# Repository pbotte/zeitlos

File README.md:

# Ladensystem für einen automatischen Dorfladen

Ein Paket aus Soft- und Hardware für ein automatisches Ladensystem, welches sich für kleine Läden, bis ca. 1000 Produkte, eignet. Das System basiert darauf, dass jedes Produkt durch eine eigene Waage gewogen wird, welche mit einem Computer verbunden ist.

## Beschreibung eines typischen Einkaufs:
1. Einlass mit Girocard oder Kreditkarte. Dabei findet eine Vorauthorisierung (Reservierung von Geld) statt.
2. Der Kunde betritt den Laden und entnimmt die Waren selbst aus den Regalen. Die Anzeige der entnommen Waren und Massen erfolgt sofort und automatisch auf den Kundendisplays.
3. Zum Abschluss des Einkaufs verlässt der Kunde den Laden. Die Abrechnung erfolgt anschließend automatisch über die Karte ohne dass die Karte erneut vorgezeigt werden muss.

Es kann immer nur ein Kunde gleichzeitig einkaufen.

## Hinweise
* [Kostenübersicht](kostenuebersicht.md)

## Technische Details 
* [Zustände eines Einkaufs](ablauf.md)
* [Bestandteile des Ladens / MQTT-Übersicht](MQTT_Overview.md)
* In den jeweiligen Unterordnern gibt es weitere Markdown-Dateien mit Erläuterungen zur Installation und Befehlen.
* Zum gleichzeitigen Herunterladen der Submodule: 
  ```bash
  git clone --recurse-submodules  git@github.com:pbotte/zeitlos.git
  ```

## Lizenz
Alle Soft- und Hardware stehen unter der [GPL v3](https://github.com/pbotte/zeitlos/blob/master/LICENSE) zur freien Verfügung.

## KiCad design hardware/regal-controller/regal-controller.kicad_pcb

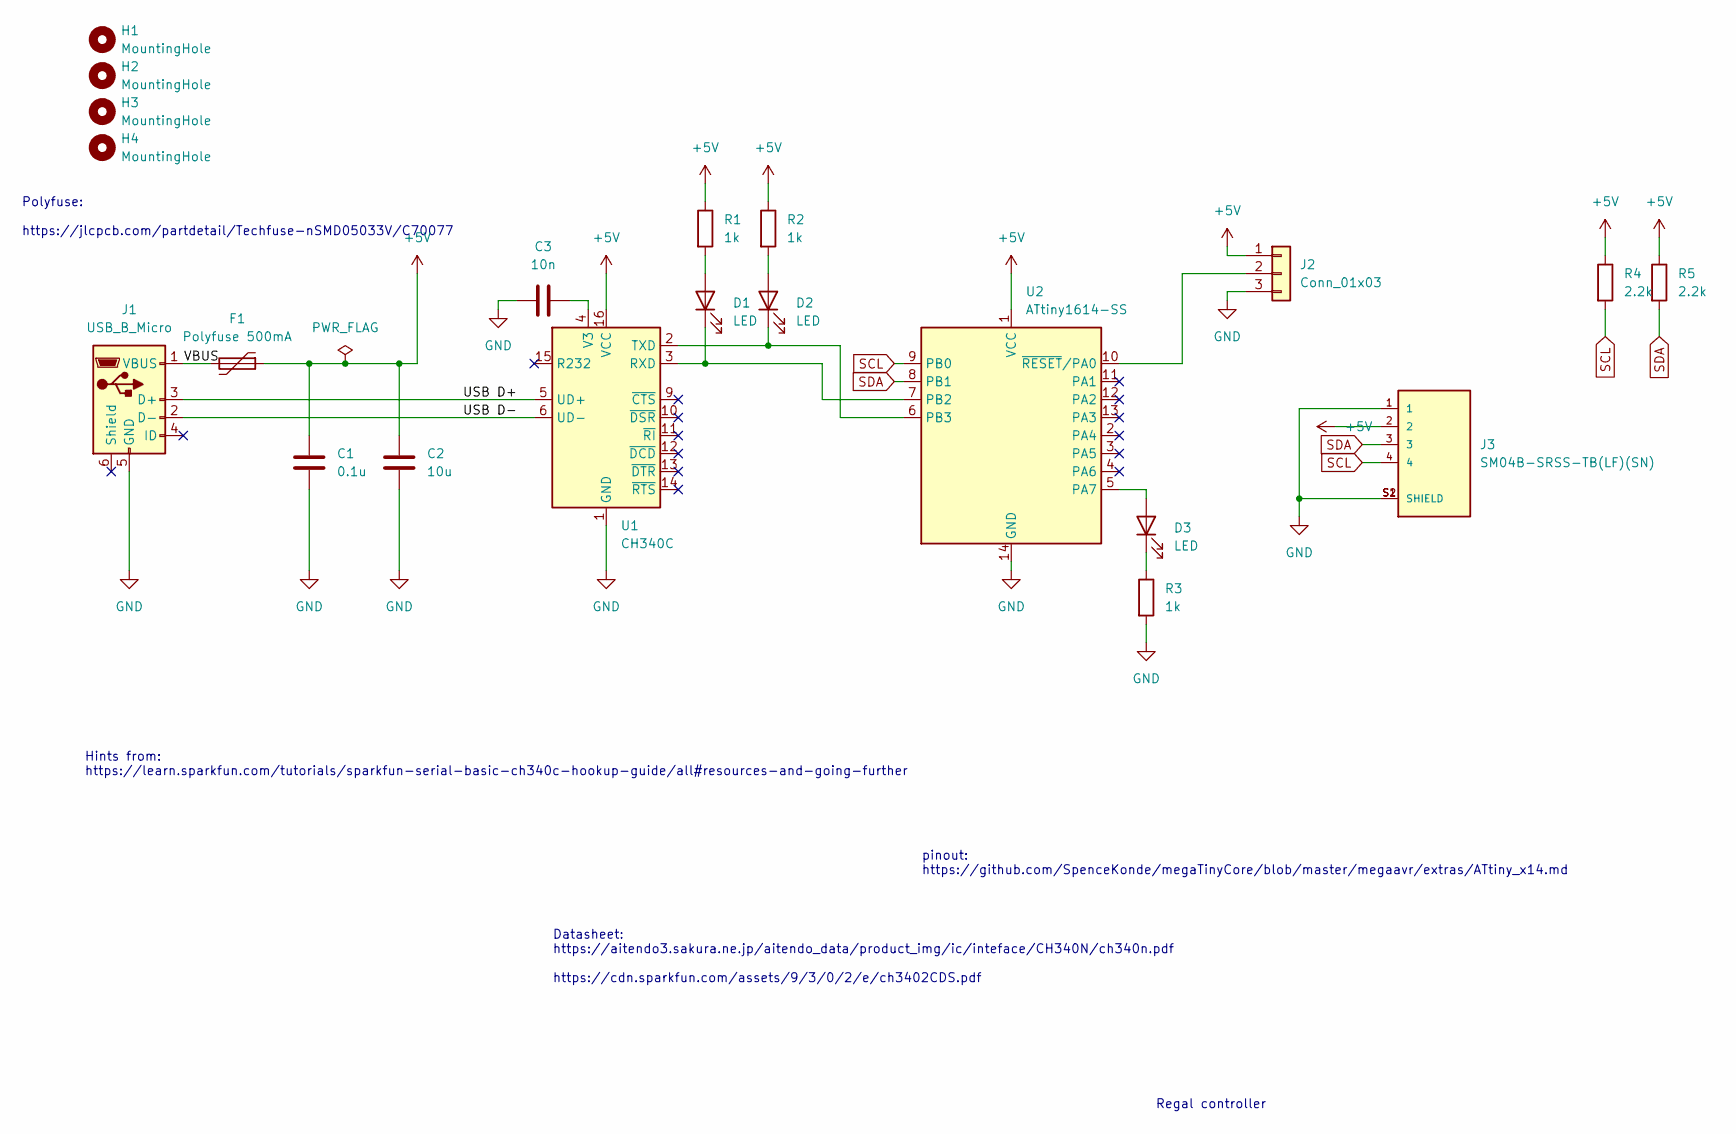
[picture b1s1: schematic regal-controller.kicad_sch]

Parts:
C1: 0.1u; C_1206_3216Metric
C2: 10u; C_1206_3216Metric
C3: 10n; C_1206_3216Metric
D1, D2, D3: LED; LED_1206_3216Metric
F1: Polyfuse 500mA; Fuse_1206_3216Metric
H1, H2, H3, H4: MountingHole; MountingHole_3.2mm_M3
J1: USB_B_Micro; USB_Micro-B_XKB_U254-051T-4BH83-F1S
J2: Conn_01x03; PinSocket_1x03_P2.54mm_Vertical
J3: SM04B-SRSS-TB(LF)(SN); JST_SM04B-SRSS-TB(LF)(SN)
R1, R2, R3: 1k; R_1206_3216Metric
R4, R5: 2.2k; R_1206_3216Metric
U1: CH340C; SOIC-16_3.9x9.9mm_P1.27mm
U2: ATtiny1614-SS; SOIC-14_3.9x8.7mm_P1.27mm

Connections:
+5V: C1.1, C2.1, F1.1, J2.1, J3.2, R1.1, R2.1, R4.1, R5.1, U1.16 (VCC), U2.1 (VCC)
/USB D+: J1.3 (D+), U1.5 (UD+)
/USB D-: J1.2 (D-), U1.6 (UD-)
/VBUS: F1.2, J1.1 (VBUS)
GND: C1.2, C2.2, C3.1, J1.5 (GND), J2.3, J3.1, J3.S1 (SHIELD), J3.S2 (SHIELD), R3.2, U1.1 (GND), U2.14 (GND)
unnamed: D1.2 (A), R1.2
unnamed: D1.1 (K), U1.3 (RXD), U2.7 (PB2)
unnamed: D2.2 (A), R2.2
unnamed: D2.1 (K), U1.2 (TXD), U2.6 (PB3)
unnamed: D3.2 (A), U2.5 (PA7)
unnamed: D3.1 (K), R3.1
unnamed: J2.2, U2.10 (~RESET/PA0)
unnamed: C3.2, U1.4 (V3)
SCL: J3.4, R4.2, U2.9 (PB0)
SDA: J3.3, R5.2, U2.8 (PB1)

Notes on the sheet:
Regal controller
pinout: https://github.com/SpenceKonde/megaTinyCore/blob/master/megaavr/extras/ATtiny_x14.md
Polyfuse: https://jlcpcb.com/partdetail/Techfuse-nSMD05033V/C70077
Datasheet: https://aitendo3.sakura.ne.jp/aitendo_data/product_img/ic/inteface/CH340N/ch340n.pdf https://cdn.sparkfun.com/assets/9/3/0/2/e/ch3402CDS.pdf
Hints from: https://learn.sparkfun.com/tutorials/sparkfun-serial-basic-ch340c-hookup-guide/all#resources-and-going-further

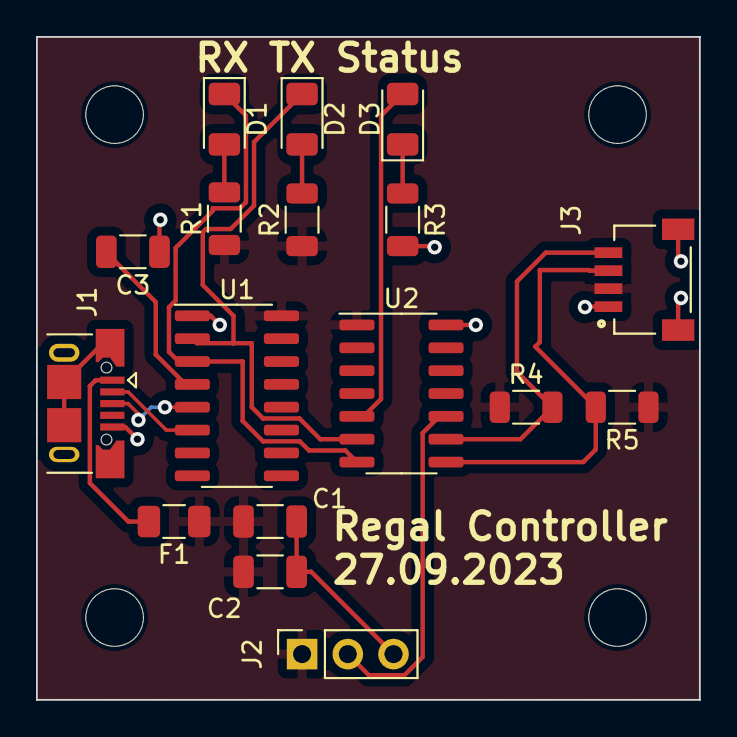
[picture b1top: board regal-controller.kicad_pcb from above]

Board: 2 copper layers, 36.8 x 36.8 mm, 21 parts (0 on the bottom side), 15 nets.

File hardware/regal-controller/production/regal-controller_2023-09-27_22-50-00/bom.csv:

Designator,Footprint,Quantity,Value,LCSC Part #
C1,1206,1,0.1u,
C2,1206,1,10u,
C3,1206,1,10n,
"D1, D2, D3",1206,3,LED,
F1,1206,1,Polyfuse 500mA,
"H1, H2, H3, H4",MountingHole_3.2mm_M3,4,MountingHole,
J1,USB_Micro-B_XKB_U254-051T-4BH83-F1S,1,USB_B_Micro,
J2,PinSocket_1x03_P2.54mm_Vertical,1,Conn_01x03,
J3,JST_SM04B-SRSS-TB(LF)(SN),1,SM04B-SRSS-TB(LF)(SN),
"R1, R2, R3",1206,3,1k,
"R4, R5",1206,2,2.2k,
U1,SOIC-16_3.9x9.9mm_P1.27mm,1,CH340C,
U2,SOIC-14_3.9x8.7mm_P1.27mm,1,ATtiny1614-SS,

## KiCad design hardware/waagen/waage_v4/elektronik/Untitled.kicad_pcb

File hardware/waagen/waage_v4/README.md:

# Waage V4

* Waage aus 3D Drucker
* Wiegen mit Wägezellen

Kosten: Etwa 25€/Waage mit Druck und Elektornik.
Stand: Prototyp, aktuell in der Entwicklung. 

3D-Daten: https://cad.onshape.com/documents/e93dca015aaa1e9e19b301b1/w/7b48b7bfd47193fa3707ac4f/e/e2c3e895b10e82bbda4e5613?renderMode=0&uiState=649b429d2a16ba7928158867

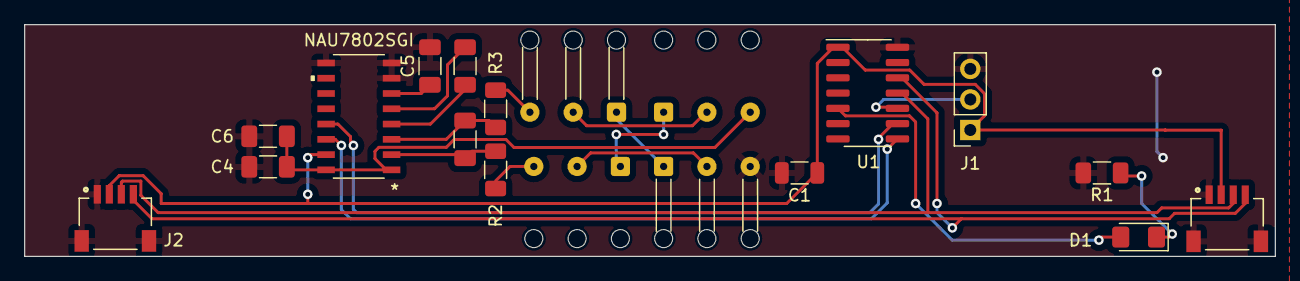
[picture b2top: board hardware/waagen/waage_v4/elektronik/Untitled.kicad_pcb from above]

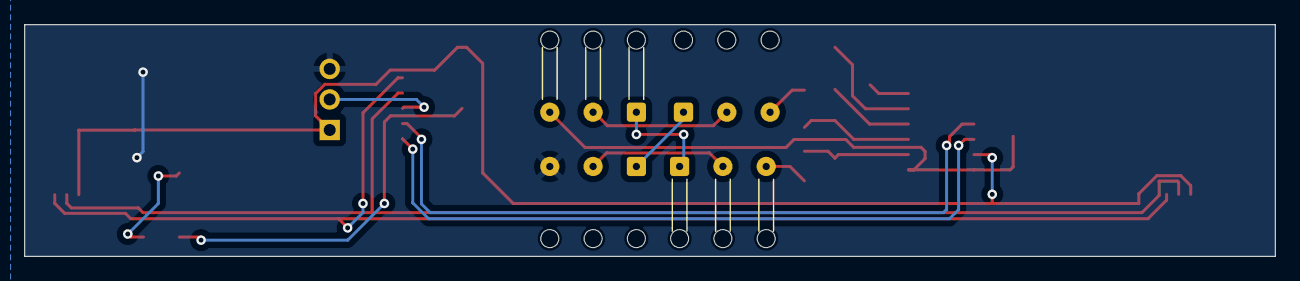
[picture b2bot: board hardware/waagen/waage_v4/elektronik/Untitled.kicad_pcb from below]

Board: 2 copper layers, 104.0 x 19.3 mm, 19 parts (2 on the bottom side), 21 nets.

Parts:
C1: 10u; C_1206_3216Metric
C2, C5, C6: 100n; C_1206_3216Metric_Pad1.33x1.80mm_HandSolder
C3: 330p; C_1206_3216Metric_Pad1.33x1.80mm_HandSolder
C4: 1µ; C_1206_3216Metric_Pad1.33x1.80mm_HandSolder
D1: LED; LED_1206_3216Metric_Pad1.42x1.75mm_HandSolder
J1: Conn_01x03; PinSocket_1x03_P2.54mm_Vertical
J2, J3: SM04B-SRSS-TB(LF)(SN); JST_SM04B-SRSS-TB(LF)(SN)
J4, J5, J6, J7: Conn_01x03_Male; SolderWire-0.1sqmm_1x03_P3.6mm_D0.4mm_OD1mm_Relief
R1: 180; R_1206_3216Metric_Pad1.30x1.75mm_HandSolder
R2, R3: 47; R_1206_3216Metric_Pad1.30x1.75mm_HandSolder
U1: ATtiny1614-SS; SOIC-14_3.9x8.7mm_P1.27mm
U2: NAU7802SGI

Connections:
/SCL_0: U1.9 (PB0), U2.13 (SCLK)
/SDA_0: U1.8 (PB1), U2.14 (SDIO)
/Scale/NAU_VDDA: C4.1, C6.1, J7.3, U2.1 (REFP), U2.16 (AVDD/LDO)
GND: C1.2, C4.2, C5.2, C6.2, J1.3, J2.1, J2.S1 (SHIELD), J2.S2 (SHIELD), J3.1, J3.S1 (SHIELD), J3.S2 (SHIELD), J4.3, R1.2, U1.14 (GND), U2.7 (REFN), U2.8 (AVSS), U2.9 (DVSS)
unnamed: D1.2 (A), U1.5 (PA7)
unnamed: D1.1 (K), R1.1
unnamed: J1.2, U1.10 (~RESET/PA0)
unnamed: J4.1, J6.1
unnamed: J4.2, J5.2
unnamed: J5.1, J7.1
unnamed: J5.3, R2.1
unnamed: J6.2, J7.2
unnamed: J6.3, R3.1
unnamed: C5.1, U2.6 (VBG)
unnamed: C2.1, R2.2, U2.2 (VIN1N)
unnamed: C2.2, R3.2, U2.3 (VIN1P)
unnamed: C3.1, U2.4 (VIN2N)
unnamed: C3.2, U2.5 (VIN2P)
SCL_1: J2.4, J3.4, U1.12 (PA2)
SDA_1: J2.3, J3.3, U1.11 (PA1)
VCC: C1.1, J1.1, J2.2, J3.2, U1.1 (VCC), U2.15 (DVDD)

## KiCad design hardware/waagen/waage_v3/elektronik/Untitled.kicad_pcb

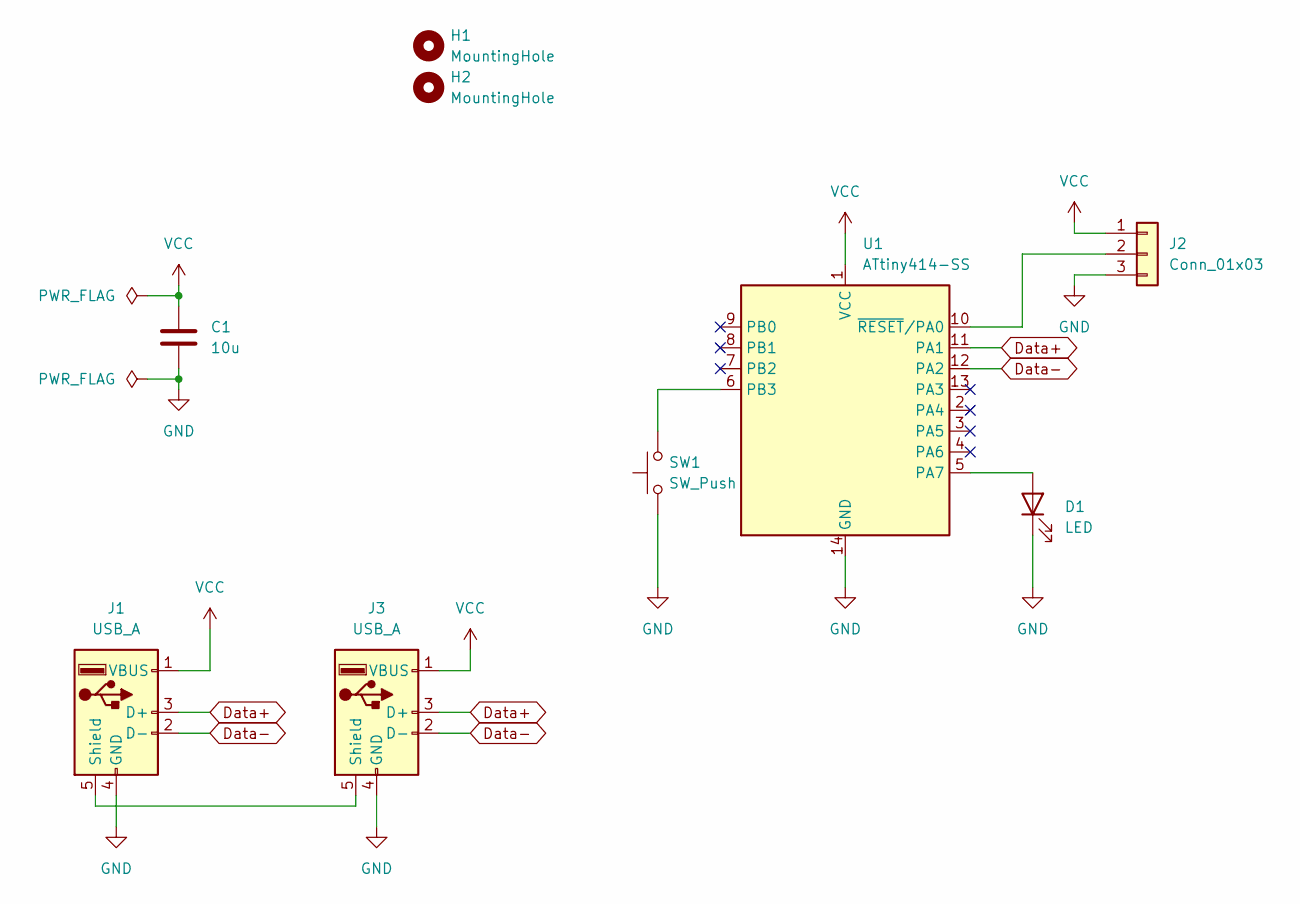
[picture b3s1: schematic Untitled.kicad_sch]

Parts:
C1: 10u; C_1206_3216Metric
D1: LED; LED_D5.0mm_Horizontal_O3.81mm_Z9.0mm
H1, H2: MountingHole; MountingHole_2.5mm
J1: USB_A; Conn_USB_A_Jack
J2: Conn_01x03; PinSocket_1x03_P2.54mm_Vertical
J3: USB_A; Conn_USB_A_Plug
SW1: SW_Push; Button_Switch_ESE-11MV1T
U1: ATtiny414-SS; SOIC-14_3.9x8.7mm_P1.27mm

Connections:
Data+: J1.3 (D+), J3.3 (D+), U1.11 (PA1)
Data-: J1.2 (D-), J3.2 (D-), U1.12 (PA2)
GND: C1.2, D1.1 (K), J1.4 (GND), J2.3, J3.4 (GND), SW1.1, U1.14 (GND)
unnamed: D1.2 (A), U1.5 (PA7)
unnamed: J1.5 (Shield), J3.5 (Shield)
unnamed: J2.2, U1.10 (~RESET/PA0)
unnamed: SW1.2, U1.6 (PB3)
VCC: C1.1, J1.1 (VBUS), J2.1, J3.1 (VBUS), U1.1 (VCC)

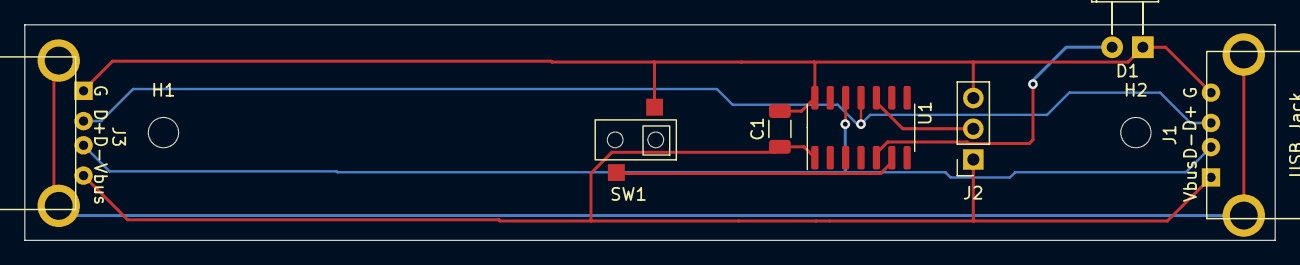
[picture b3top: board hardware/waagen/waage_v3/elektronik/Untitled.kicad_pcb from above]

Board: 2 copper layers, 103.2 x 17.8 mm, 9 parts (0 on the bottom side), 8 nets.

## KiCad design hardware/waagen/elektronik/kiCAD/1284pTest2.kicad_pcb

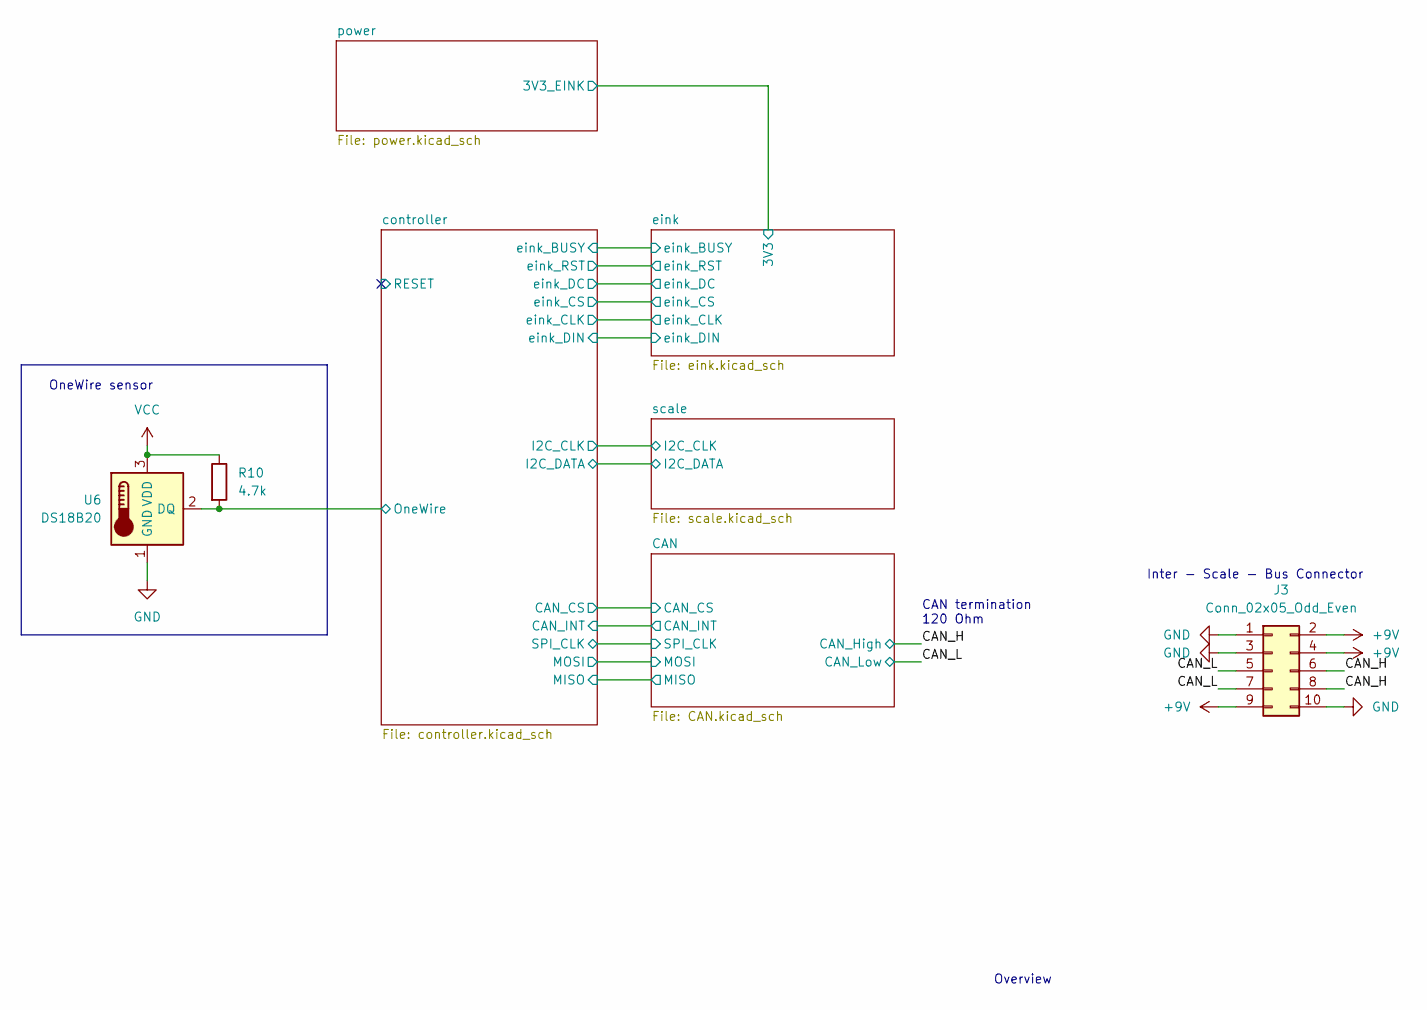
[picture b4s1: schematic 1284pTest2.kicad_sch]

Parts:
J3: Conn_02x05_Odd_Even; PinSocket_2x05_P2.54mm_Horizontal
R10: 4.7k; R_1206_3216Metric_Pad1.30x1.75mm_HandSolder
U6: DS18B20; TO-92

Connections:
+9V: J3.2, J3.4, J3.9; also elsewhere on the board
/CAN_H: J3.6, J3.8; also elsewhere on the board
/CAN_L: J3.5, J3.7; also elsewhere on the board
/controller/OneWire: R10.2, U6.2 (DQ); also elsewhere on the board
GND: J3.1, J3.3, J3.10, U6.1 (GND); also elsewhere on the board
VCC: R10.1, U6.3 (VDD); also elsewhere on the board

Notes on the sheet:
CAN termination 120 Ohm
Inter - Scale - Bus Connector
Overview
OneWire sensor

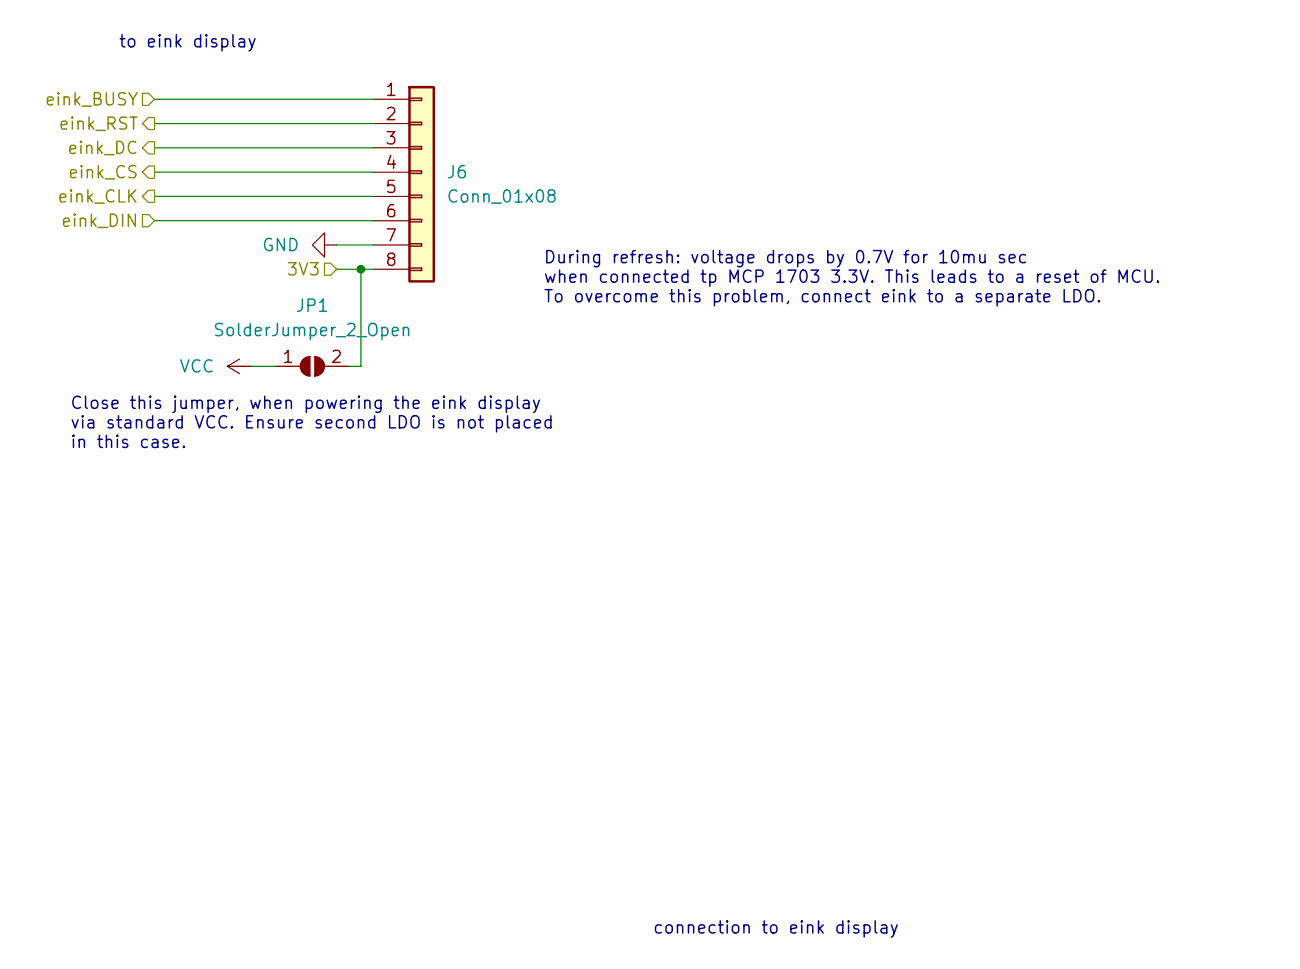
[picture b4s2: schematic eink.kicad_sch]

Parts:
J6: Conn_01x08; PinHeader_1x08_P2.54mm_Horizontal
JP1: SolderJumper_2_Open; SolderJumper-2_P1.3mm_Open_RoundedPad1.0x1.5mm

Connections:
/controller/eink_BUSY: J6.1; also elsewhere on the board
/controller/eink_CLK: J6.5; also elsewhere on the board
/controller/eink_CS: J6.4; also elsewhere on the board
/controller/eink_DC: J6.3; also elsewhere on the board
/controller/eink_DIN: J6.6; also elsewhere on the board
/controller/eink_RST: J6.2; also elsewhere on the board
/power/3V3_EINK: J6.8, JP1.2 (B); also elsewhere on the board
GND: J6.7; also elsewhere on the board
VCC: JP1.1 (A); also elsewhere on the board

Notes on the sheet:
to eink display
Close this jumper, when powering the eink display via standard VCC. Ensure second LDO is not placed in this case.
During refresh: voltage drops by 0.7V for 10mu sec when connected tp MCP 1703 3.3V. This leads to a reset of MCU. To overcome this problem, connect eink to a separate LDO.
connection to eink display

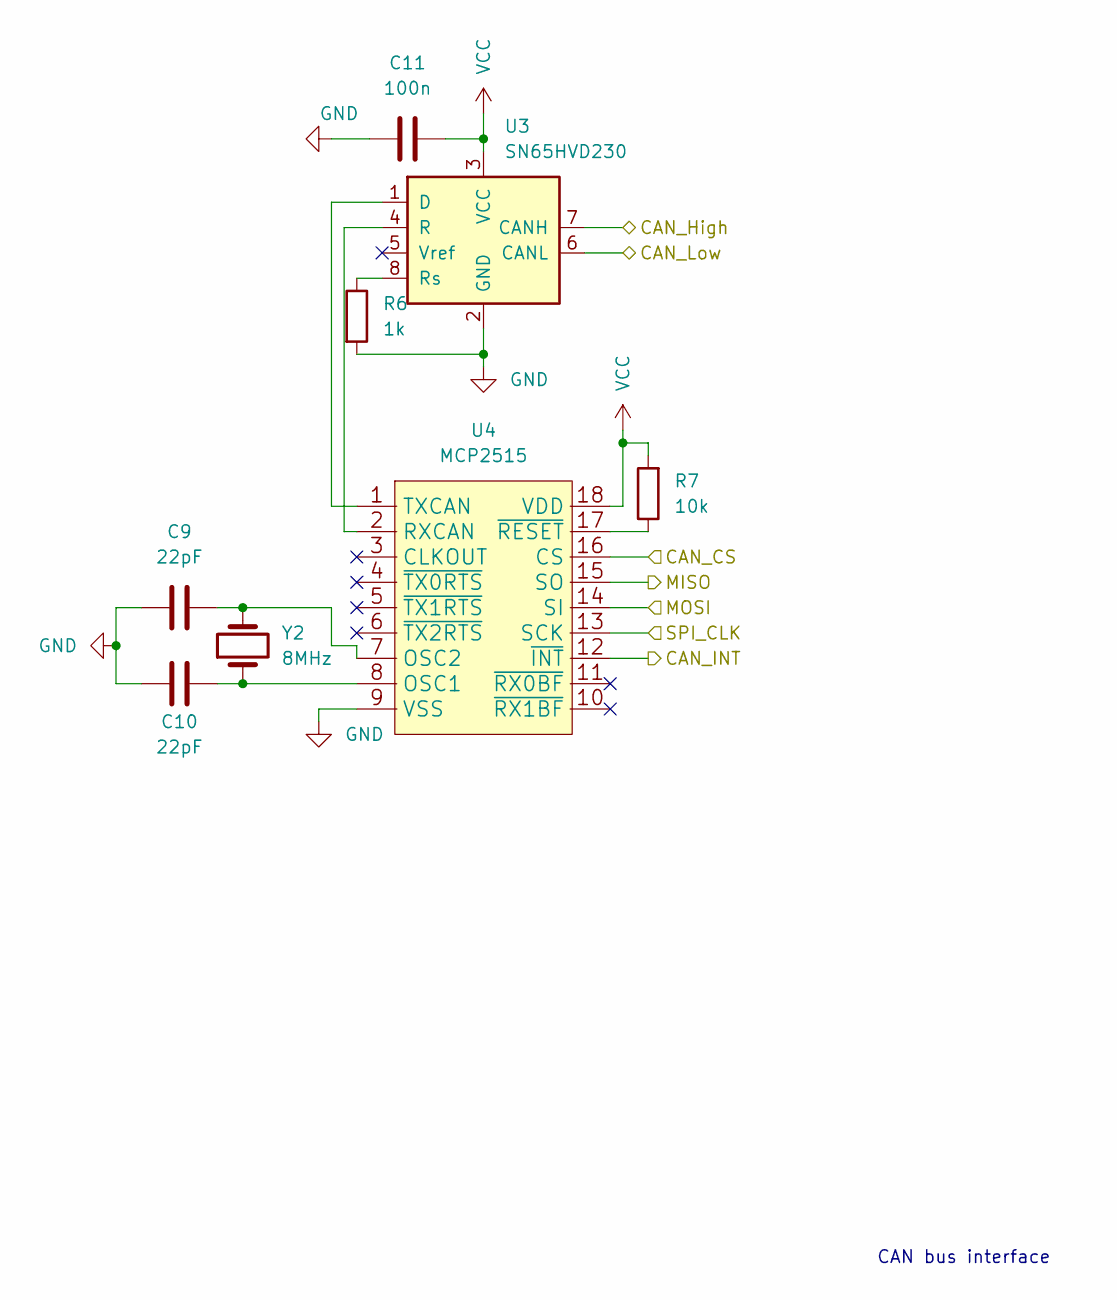
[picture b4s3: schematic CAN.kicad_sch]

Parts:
C9, C10: 22pF; C_1206_3216Metric_Pad1.33x1.80mm_HandSolder
C11: 100n; C_1206_3216Metric_Pad1.33x1.80mm_HandSolder
R6: 1k; R_1206_3216Metric_Pad1.30x1.75mm_HandSolder
R7: 10k; R_1206_3216Metric_Pad1.30x1.75mm_HandSolder
U3: SN65HVD230; SOIC-8_3.9x4.9mm_P1.27mm
U4: MCP2515; DIP-18_W7.62mm_LongPads
Y2: 8MHz; Crystal_SMD_HC49-SD

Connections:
/CAN/CAN_CS: U4.16 (CS); also elsewhere on the board
/CAN/CAN_INT: U4.12 (~INT); also elsewhere on the board
/CAN/MISO: U4.15 (SO); also elsewhere on the board
/CAN/MOSI: U4.14 (SI); also elsewhere on the board
/CAN/SPI_CLK: U4.13 (SCK); also elsewhere on the board
/CAN_H: U3.7 (CANH); also elsewhere on the board
/CAN_L: U3.6 (CANL); also elsewhere on the board
GND: C9.1, C10.1, C11.1, R6.2, U3.2 (GND), U4.9 (VSS); also elsewhere on the board
unnamed: C9.2, U4.7 (OSC2), Y2.2
unnamed: C10.2, U4.8 (OSC1), Y2.1
unnamed: R6.1, U3.8 (Rs)
unnamed: R7.1, U4.17 (~RESET)
unnamed: U3.1 (D), U4.1 (TXCAN)
unnamed: U3.4 (R), U4.2 (RXCAN)
VCC: C11.2, R7.2, U3.3 (VCC), U4.18 (VDD); also elsewhere on the board

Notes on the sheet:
CAN bus interface

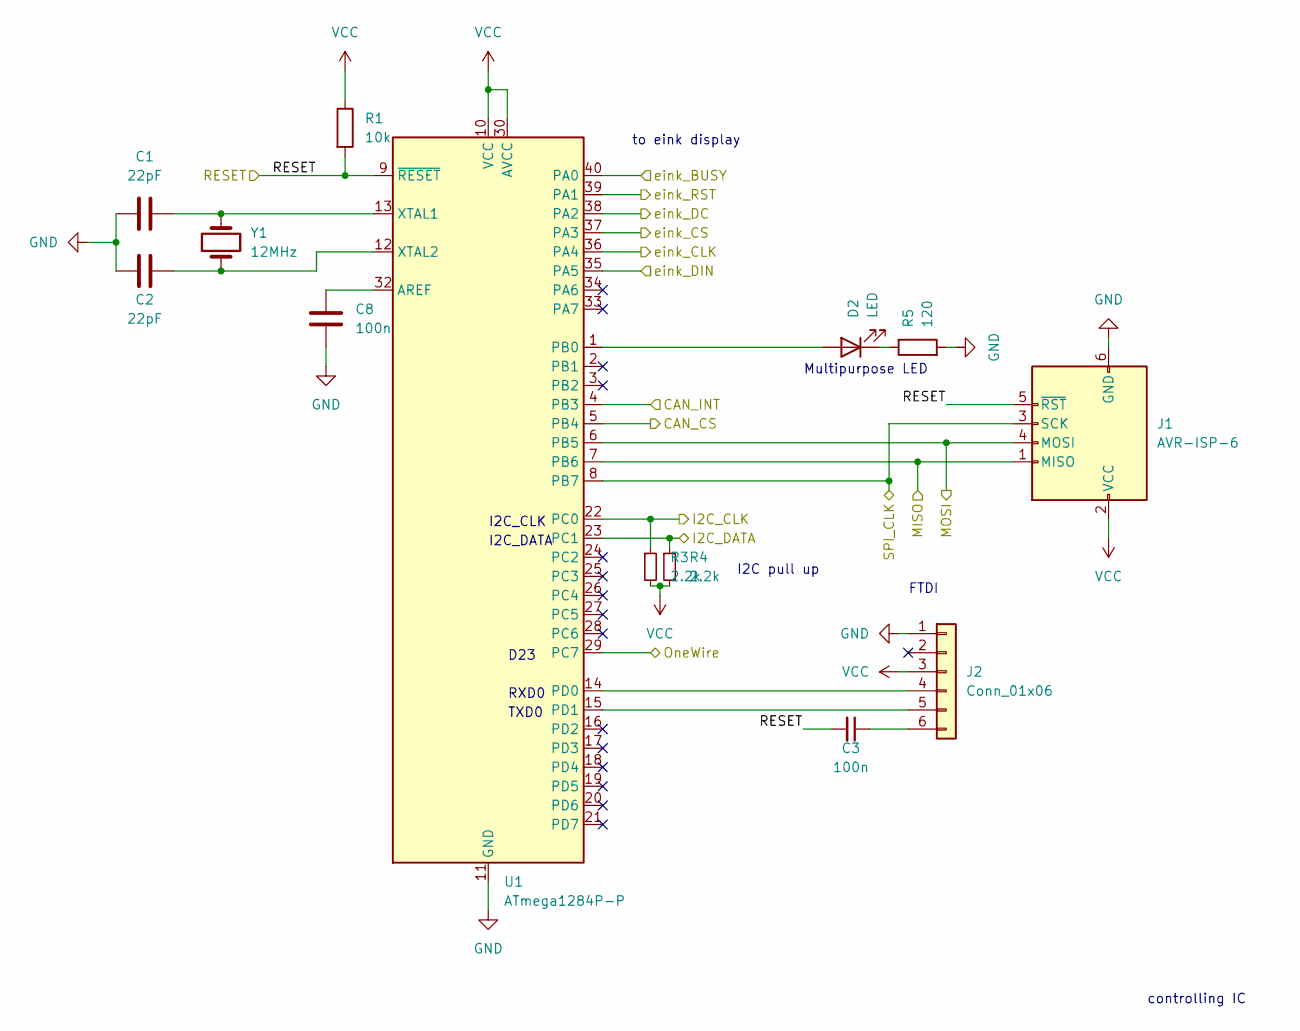
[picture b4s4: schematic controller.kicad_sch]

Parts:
C1, C2: 22pF; C_1206_3216Metric_Pad1.33x1.80mm_HandSolder
C3, C8: 100n; C_1206_3216Metric_Pad1.33x1.80mm_HandSolder
D2: LED; LED_1206_3216Metric_Pad1.42x1.75mm_HandSolder
J1: AVR-ISP-6; PinSocket_2x03_P2.54mm_Vertical
J2: Conn_01x06; PinSocket_1x06_P2.54mm_Vertical
R1: 10k; R_1206_3216Metric_Pad1.30x1.75mm_HandSolder
R3, R4: 2.2k; R_1206_3216Metric_Pad1.30x1.75mm_HandSolder
R5: 120; R_1206_3216Metric_Pad1.30x1.75mm_HandSolder
U1: ATmega1284P-P; DIP-40_W15.24mm
Y1: 12MHz; Crystal_SMD_HC49-SD_HandSoldering

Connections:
/CAN/CAN_CS: U1.5 (PB4); also elsewhere on the board
/CAN/CAN_INT: U1.4 (PB3); also elsewhere on the board
/CAN/MISO: J1.1 (MISO), U1.7 (PB6); also elsewhere on the board
/CAN/MOSI: J1.4 (MOSI), U1.6 (PB5); also elsewhere on the board
/CAN/SPI_CLK: J1.3 (SCK), U1.8 (PB7); also elsewhere on the board
/controller/I2C_CLK: R3.1, U1.22 (PC0); also elsewhere on the board
/controller/I2C_DATA: R4.1, U1.23 (PC1); also elsewhere on the board
/controller/OneWire: U1.29 (PC7); also elsewhere on the board
/controller/RESET: C3.2, J1.5 (~RST), R1.2, U1.9 (~RESET)
/controller/eink_BUSY: U1.40 (PA0); also elsewhere on the board
/controller/eink_CLK: U1.36 (PA4); also elsewhere on the board
/controller/eink_CS: U1.37 (PA3); also elsewhere on the board
/controller/eink_DC: U1.38 (PA2); also elsewhere on the board
/controller/eink_DIN: U1.35 (PA5); also elsewhere on the board
/controller/eink_RST: U1.39 (PA1); also elsewhere on the board
GND: C1.1, C2.1, C8.2, J1.6 (GND), J2.1, R5.2, U1.11 (GND), U1.31 (GND); also elsewhere on the board
unnamed: C1.2, U1.13 (XTAL1), Y1.2
unnamed: C2.2, U1.12 (XTAL2), Y1.1
unnamed: C3.1, J2.6
unnamed: C8.1, U1.32 (AREF)
unnamed: D2.1 (K), R5.1
unnamed: D2.2 (A), U1.1 (PB0)
unnamed: J2.4, U1.14 (PD0)
unnamed: J2.5, U1.15 (PD1)
VCC: J1.2 (VCC), J2.3, R1.1, R3.2, R4.2, U1.10 (VCC), U1.30 (AVCC); also elsewhere on the board

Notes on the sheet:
I2C pull up
Multipurpose LED
I2C_DATA
to eink display
FTDI
TXD0
D23
controlling IC
RXD0
I2C_CLK

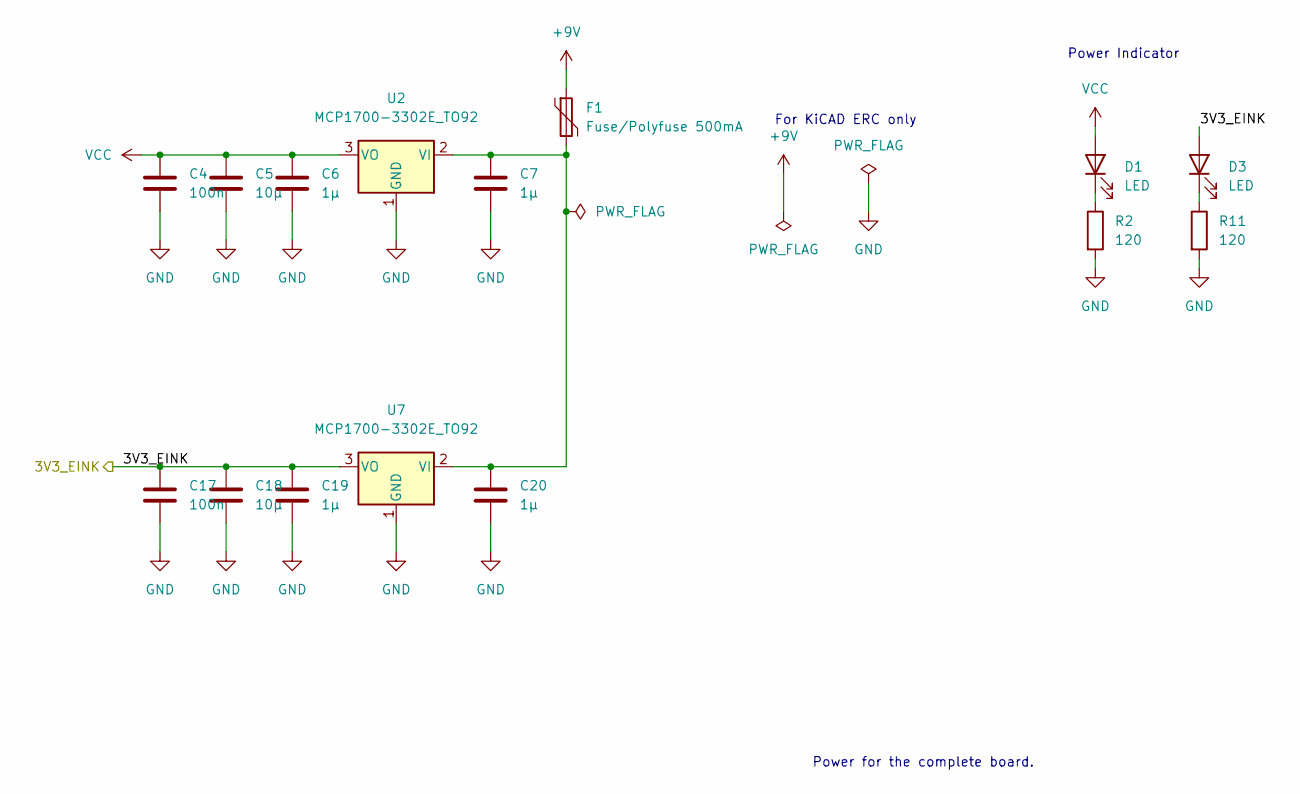
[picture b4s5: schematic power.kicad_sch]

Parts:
C4, C17: 100n; C_1206_3216Metric_Pad1.33x1.80mm_HandSolder
C5, C18: 10µ; C_1206_3216Metric_Pad1.33x1.80mm_HandSolder
C6, C7, C19, C20: 1µ; C_1206_3216Metric_Pad1.33x1.80mm_HandSolder
D1, D3: LED; LED_1206_3216Metric_Pad1.42x1.75mm_HandSolder
F1: Fuse/Polyfuse 500mA; Fuse_2512_6332Metric_Pad1.52x3.35mm_HandSolder
R2, R11: 120; R_1206_3216Metric_Pad1.30x1.75mm_HandSolder
U2, U7: MCP1700-3302E_TO92; TO-92_Inline

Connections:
+9V: F1.1; also elsewhere on the board
/power/3V3_EINK: C17.1, C18.1, C19.1, D3.2 (A), U7.3 (VO); also elsewhere on the board
GND: C4.2, C5.2, C6.2, C7.2, C17.2, C18.2, C19.2, C20.2, R2.2, R11.2, U2.1 (GND), U7.1 (GND); also elsewhere on the board
unnamed: C7.1, C20.1, F1.2, U2.2 (VI), U7.2 (VI)
unnamed: D1.1 (K), R2.1
unnamed: D3.1 (K), R11.1
VCC: C4.1, C5.1, C6.1, D1.2 (A), U2.3 (VO); also elsewhere on the board

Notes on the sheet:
For KiCAD ERC only
Power Indicator
Power for the complete board.

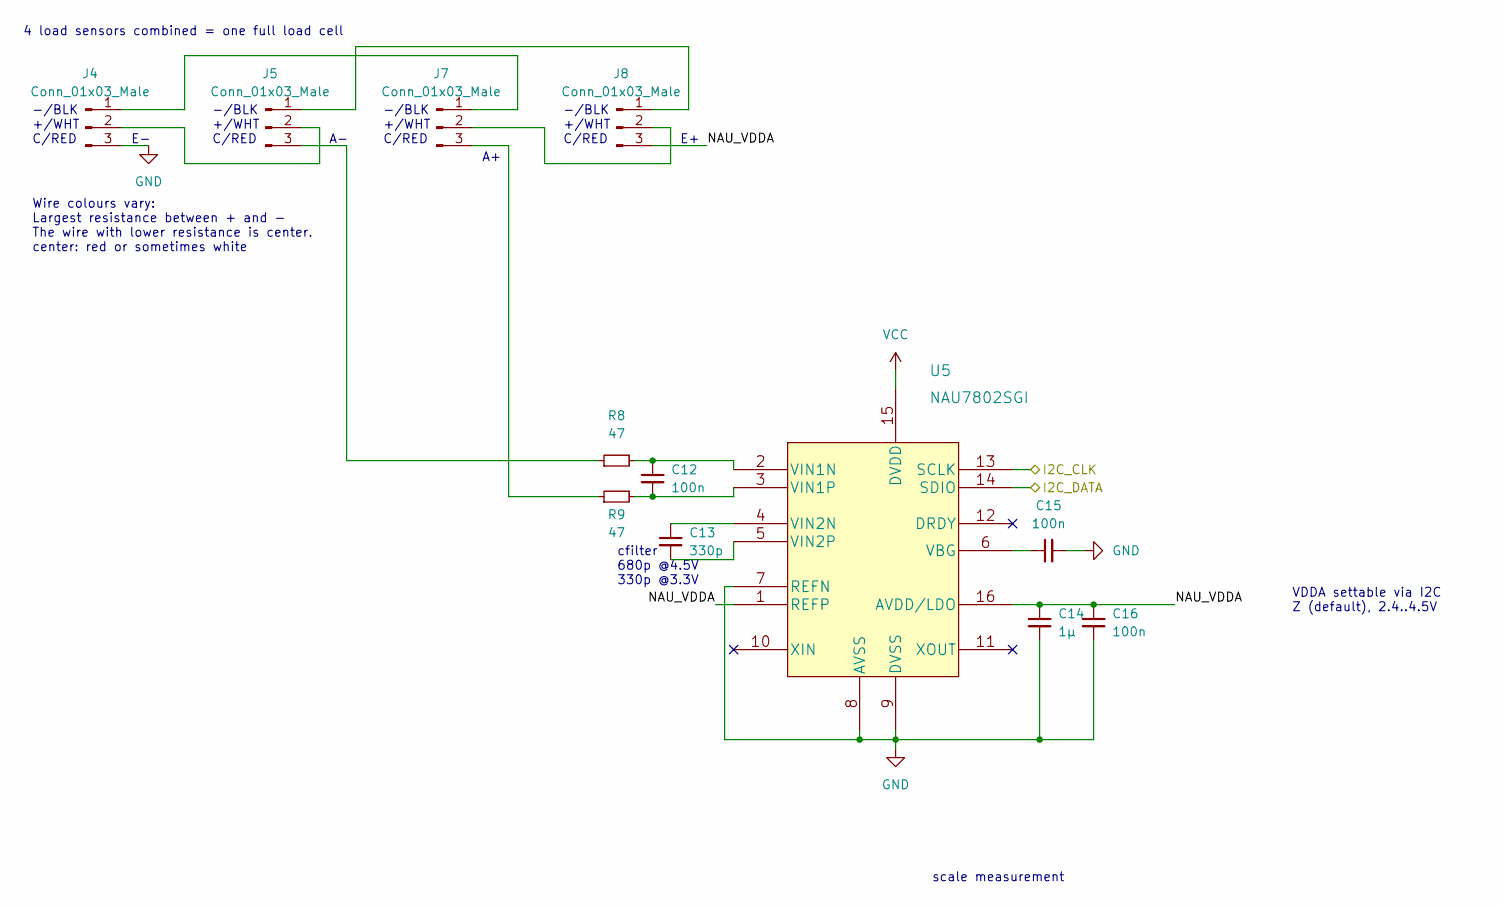
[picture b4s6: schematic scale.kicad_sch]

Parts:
C12, C15, C16: 100n; C_1206_3216Metric_Pad1.33x1.80mm_HandSolder
C13: 330p; C_1206_3216Metric_Pad1.33x1.80mm_HandSolder
C14: 1µ; C_1206_3216Metric_Pad1.33x1.80mm_HandSolder
J4, J5, J7, J8: Conn_01x03_Male; PinHeader_1x03_P2.54mm_Vertical
R8, R9: 47; R_1206_3216Metric_Pad1.30x1.75mm_HandSolder
U5: NAU7802SGI

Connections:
/controller/I2C_CLK: U5.13 (SCLK); also elsewhere on the board
/controller/I2C_DATA: U5.14 (SDIO); also elsewhere on the board
/scale/NAU_VDDA: C14.1, C16.1, J8.3, U5.1 (REFP), U5.16 (AVDD/LDO)
GND: C14.2, C15.2, C16.2, J4.3, U5.7 (REFN), U5.8 (AVSS), U5.9 (DVSS); also elsewhere on the board
unnamed: C12.1, R8.2, U5.2 (VIN1N)
unnamed: C12.2, R9.2, U5.3 (VIN1P)
unnamed: C13.1, U5.4 (VIN2N)
unnamed: C13.2, U5.5 (VIN2P)
unnamed: C15.1, U5.6 (VBG)
unnamed: J4.1, J7.1
unnamed: J4.2, J5.2
unnamed: J5.1, J8.1
unnamed: J5.3, R8.1
unnamed: J7.2, J8.2
unnamed: J7.3, R9.1
VCC: U5.15 (DVDD); also elsewhere on the board

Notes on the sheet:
-/BLK +/WHT C/RED
cfilter 680p @4.5V 330p @3.3V
VDDA settable via I2C Z (default), 2.4..4.5V
Wire colours vary: Largest resistance between + and - The wire with lower resistance is center. center: red or sometimes white
scale measurement
4 load sensors combined = one full load cell

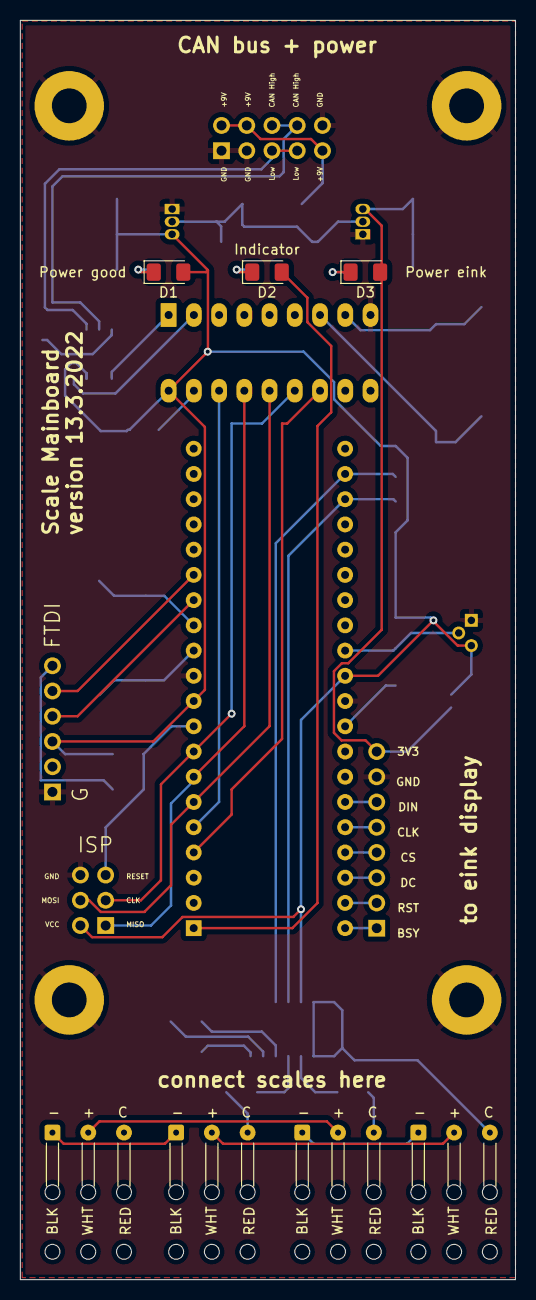
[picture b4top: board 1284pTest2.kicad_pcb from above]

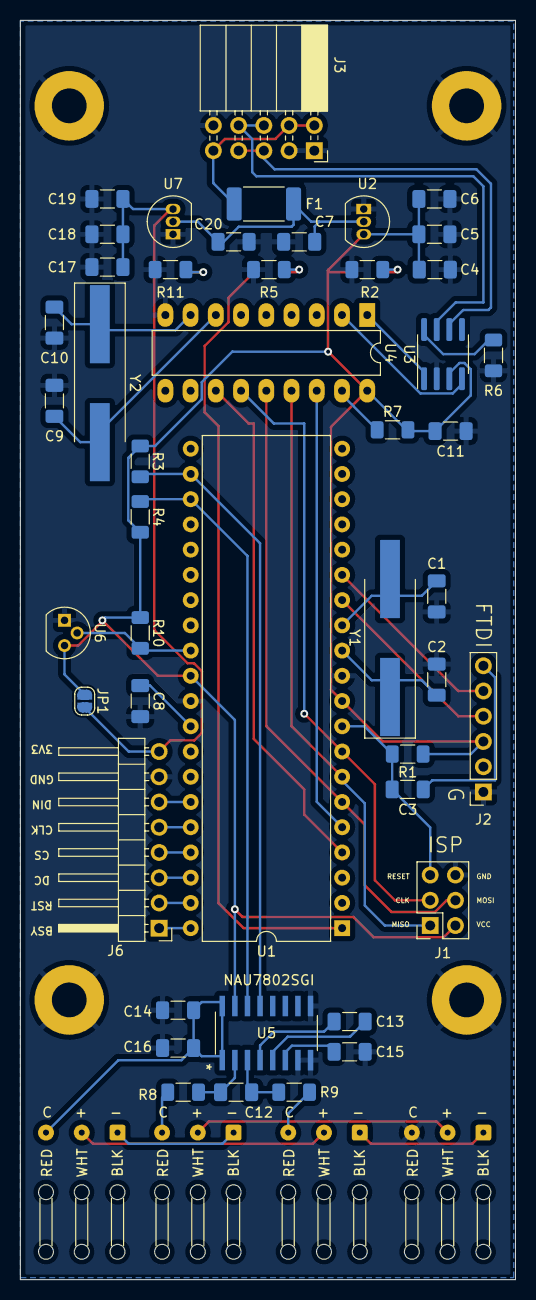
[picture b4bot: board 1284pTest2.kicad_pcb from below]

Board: 2 copper layers, 49.8 x 126.8 mm, 53 parts (46 on the bottom side), 50 nets.

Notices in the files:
parts and their libraries:
Copyright 2021 Accelerated Designs. All rights reserved.
